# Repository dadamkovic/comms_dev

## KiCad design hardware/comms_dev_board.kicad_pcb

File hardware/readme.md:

# USB/UART Interface Development Board

## Project goal
USB demonstrator will serve as a development platform for the creation of a standard USB
interface for sending and receiving data from ECUs.

In the end, the developed USB_Debug SW module should serve as a framework for
integrating simple USB and/or UART communication into my projects to assist during the
development phase.

## HW
The intention is to develop the interface to be used with HAL (STM). However, I will attempt
to separate the target-specific implementation as much as possible from the logic of the interface.

Board offers:
--------------
- 3 LEDs for debugging purposes
- UART Interface
- Debug/programming interface
- USB Interface 
- STM32F042f4Px as uC of choice
- switch for selecting the power source UART / USB (to prevent issues if both connected at once)

## Current Status
HW design is completed and should be sufficient to begin the development. 
There are a few other development modules I plan to prepare and order at once to save on postage.

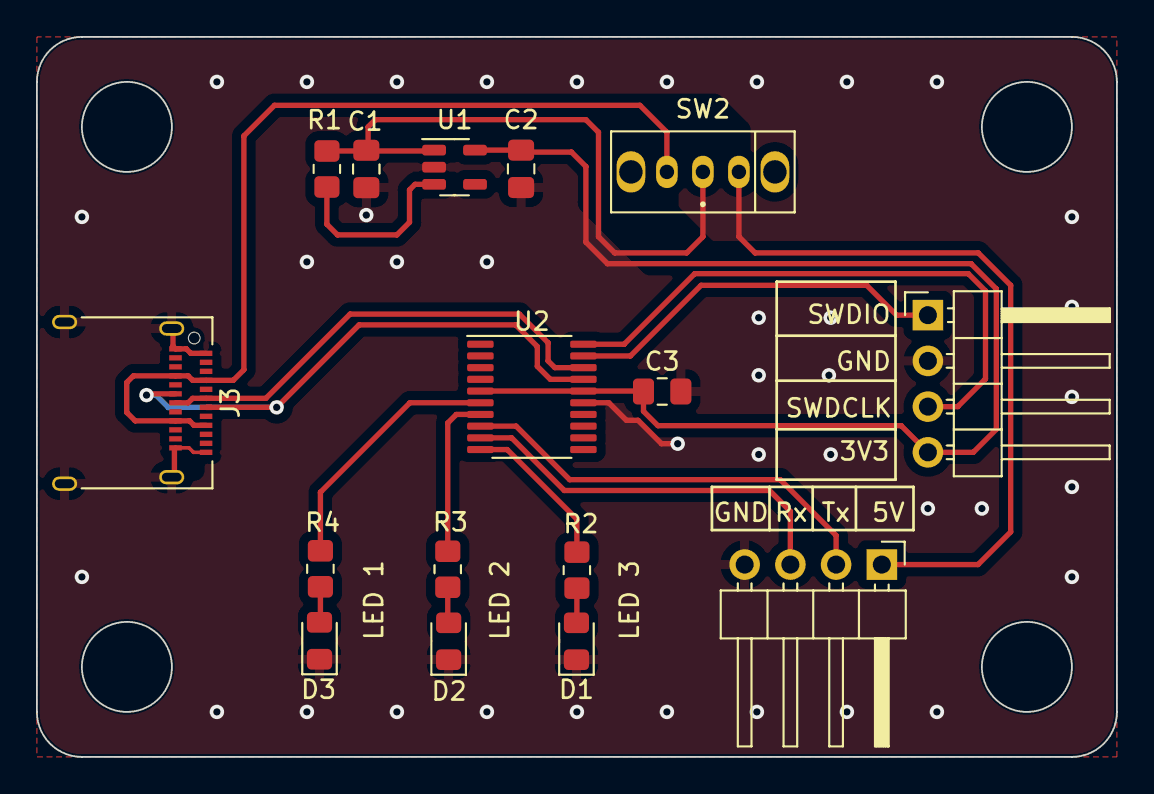
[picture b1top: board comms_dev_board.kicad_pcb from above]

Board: 2 copper layers, 60.0 x 40.0 mm, 16 parts (0 on the bottom side), 18 nets.

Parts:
C1, C2, C3: 1u; C_0805_2012Metric_Pad1.18x1.45mm_HandSolder
D1, D2, D3: LED; LED_0805_2012Metric_Pad1.15x1.40mm_HandSolder
J1, J2: Conn_01x04_Pin; PinHeader_1x04_P2.54mm_Horizontal
J3: USB_C_Receptacle_USB2.0; USB_C_Receptacle_Amphenol_12401610E4-2A
R1: 2k; R_0805_2012Metric_Pad1.20x1.40mm_HandSolder
R2, R3, R4: 660R; R_0805_2012Metric_Pad1.20x1.40mm_HandSolder
SW2: EG 1248
U1: MIC5504-1.2YM5; SOT-23-5
U2: STM32F042F4Px; TSSOP-20_4.4x6.5mm_P0.65mm

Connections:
GND: C1.2, C2.2, C3.2, D1.1 (K), D2.1 (K), D3.1 (K), J1.2, J2.4, J3.A1 (GND), J3.A12 (GND), J3.B1 (GND), J3.B12 (GND), J3.S1 (SHIELD), U1.2 (GND), U2.15 (VSSA)
unnamed: D1.2 (A), R2.2
unnamed: D2.2 (A), R3.2
unnamed: D3.2 (A), R4.2
unnamed: R1.1, U1.3 (EN)
unnamed: R4.1, U2.6 (PA0)
unnamed: R3.1, U2.7 (PA1)
unnamed: R2.1, U2.10 (PA4)
SWDCLK: J1.3, U2.20 (PA14)
SWDIO: J1.1, U2.19 (PA13)
SYSTEM_3V3: C2.1, C3.1, J1.4, U1.5 (VOUT), U2.5 (VDDA), U2.16 (VDD)
SYSTEM_5V: C1.1, R1.2, SW2.2 (B), U1.1 (VIN)
UART_SUPP_5V: J2.1, SW2.1 (A)
USART_Rx: J2.3, U2.9 (PA3)
USART_Tx: J2.2, U2.8 (PA2)
USB_COMM_D+: J3.A6 (D+), J3.B6 (D+), U2.18 (PA10/PA12)
USB_COMM_D-: J3.A7 (D-), J3.B7 (D-), U2.17 (PA9/PA11)
USB_SUPP_5V: J3.A4 (VBUS), J3.A9 (VBUS), J3.B4 (VBUS), J3.B9 (VBUS), SW2.3 (C)

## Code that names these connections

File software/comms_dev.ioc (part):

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Mcu.Name=STM32F042F6Px
Mcu.Package=TSSOP20
Mcu.UserName=STM32F042F6Px
PA0.GPIOParameters=GPIO_Label
PA0.GPIO_Label=LED0
PA0.Signal=GPIO_Output
PA1.GPIOParameters=GPIO_Label
PA1.GPIO_Label=LED1
PA1.Signal=GPIO_Output
PA11.Mode=Device
PA11.Signal=USB_DM
PA12.Mode=Device
PA12.Signal=USB_DP
PA13.Mode=Serial_Wire
PA13.Signal=SYS_SWDIO
PA14.Mode=Serial_Wire
PA14.Signal=SYS_SWCLK
PA2.Mode=Asynchronous
PA2.Signal=USART2_TX
PA3.Mode=Asynchronous
PA3.Signal=USART2_RX
PA4.GPIOParameters=GPIO_Label
PA4.GPIO_Label=LED2
PA4.Signal=GPIO_Output
PB1.Signal=S_TIM3_CH4
RCC.SYSCLKFreq_VALUE=48000000
RCC.SYSCLKSource=RCC_SYSCLKSOURCE_HSI48
board=custom

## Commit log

2023-09-30 Reoragnization of the project files.
2024-02-18 Re-structured repo files
